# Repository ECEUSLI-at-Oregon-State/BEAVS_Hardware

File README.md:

# BEAVS_hardware

Directory contains all KiCad files for designing the BEAVS PCB.
By using these files, one can continue modifying the existing design.

All .pretty files are footprints of the devices that are the names of the files.
Back and Front png files show 3D screenshots of the front and back of the PCB design.
Additionally, all USLI BEAVS 2020 files refer to the overall PCB design from the schematic to layout.

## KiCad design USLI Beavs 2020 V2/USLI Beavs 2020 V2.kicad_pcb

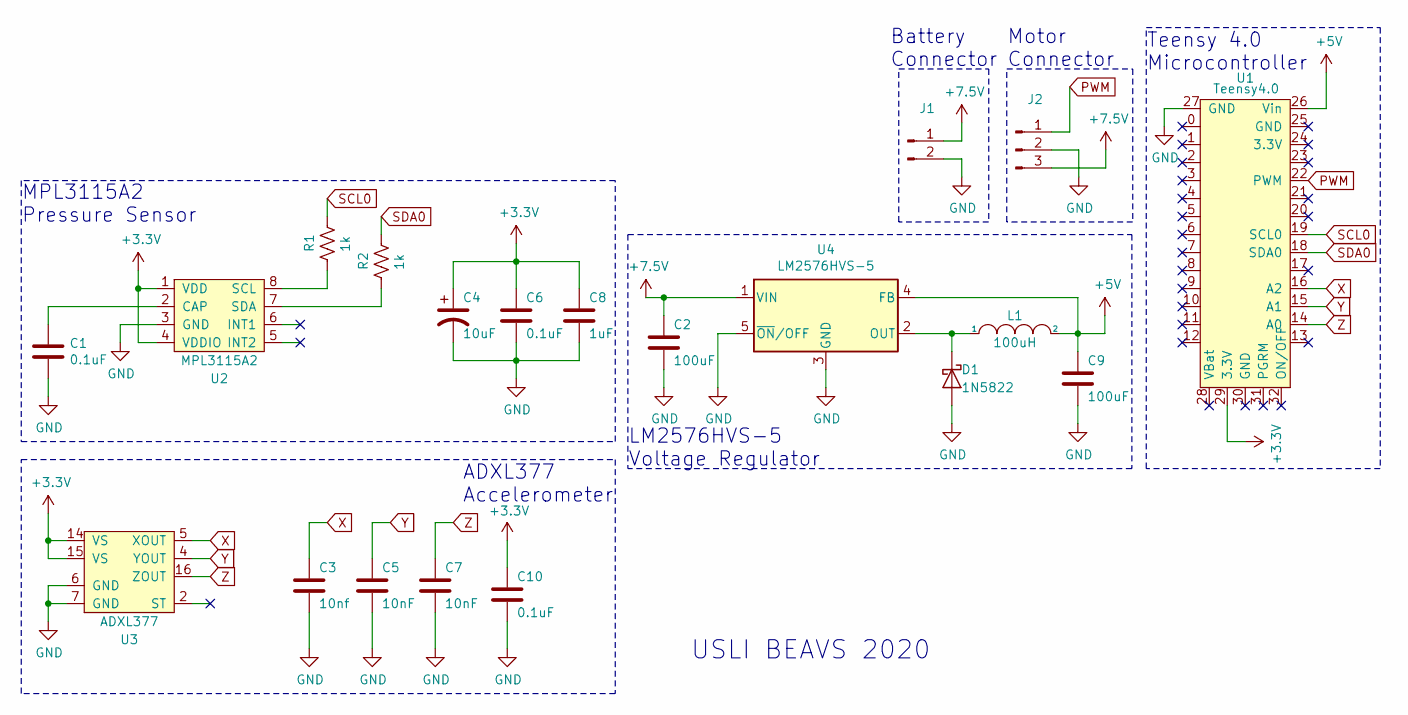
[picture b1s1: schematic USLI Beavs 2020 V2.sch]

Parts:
C1, C6, C10: 0.1uF; C_0805_2012Metric_Pad1.15x1.40mm_HandSolder
C2, C9: 100uF; elect_capacitors
C3: 10nf; C_0805_2012Metric_Pad1.15x1.40mm_HandSolder
C4: 10uF; C_0805_2012Metric_Pad1.15x1.40mm_HandSolder
C5, C7: 10nF; C_0805_2012Metric_Pad1.15x1.40mm_HandSolder
C8: 1uF; C_0805_2012Metric_Pad1.15x1.40mm_HandSolder
D1: 1N5822; IN5822
J1: vas_1x2_screw_terminal
J2: 1x3_screw_terminal
L1: 100uH; dummythiccinductor
R1, R2: 1k; R_0805_2012Metric_Pad1.15x1.40mm_HandSolder
U1: Teensy4.0; Teensy40
U2: MPL3115A2
U3: ADXL377
U4: LM2576HVS-5; TO-263-5_TabPin3

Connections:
+3V3: C4.1, C6.1, C8.1, C10.1, U1.29 (3.3V), U2.1 (VDD), U2.4 (VDDIO), U3.14 (VS), U3.15 (VS)
+5V: C9.1, L1.2, U1.26 (Vin), U4.4 (FB)
+7.5V: C2.1, J1.1, J2.3, U4.1 (VIN)
GND: C1.2, C2.2, C3.2, C4.2, C5.2, C6.2, C7.2, C8.2, C9.2, C10.2, D1.2 (A), J1.2, J2.2, U1.27 (GND), U2.3 (GND), U3.6 (GND), U3.7 (GND), U4.3 (GND), U4.5 (~ON~/OFF)
unnamed: C1.1, U2.2 (CAP)
unnamed: D1.1 (K), L1.1, U4.2 (OUT)
unnamed: R1.2, U2.8 (SCL)
unnamed: R2.2, U2.7 (SDA)
PWM: J2.1, U1.22 (PWM)
SCL0: R1.1, U1.19 (SCL0)
SDA0: R2.1, U1.18 (SDA0)
X: C3.1, U1.16 (A2), U3.5 (XOUT)
Y: C5.1, U1.15 (A1), U3.4 (YOUT)
Z: C7.1, U1.14 (A0), U3.16 (ZOUT)

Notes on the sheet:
USLI BEAVS 2020
LM2576HVS-5 Voltage Regulator
MPL3115A2 Pressure Sensor
ADXL377 Accelerometer
Teensy 4.0 Microcontroller
Battery Connector
Motor Connector

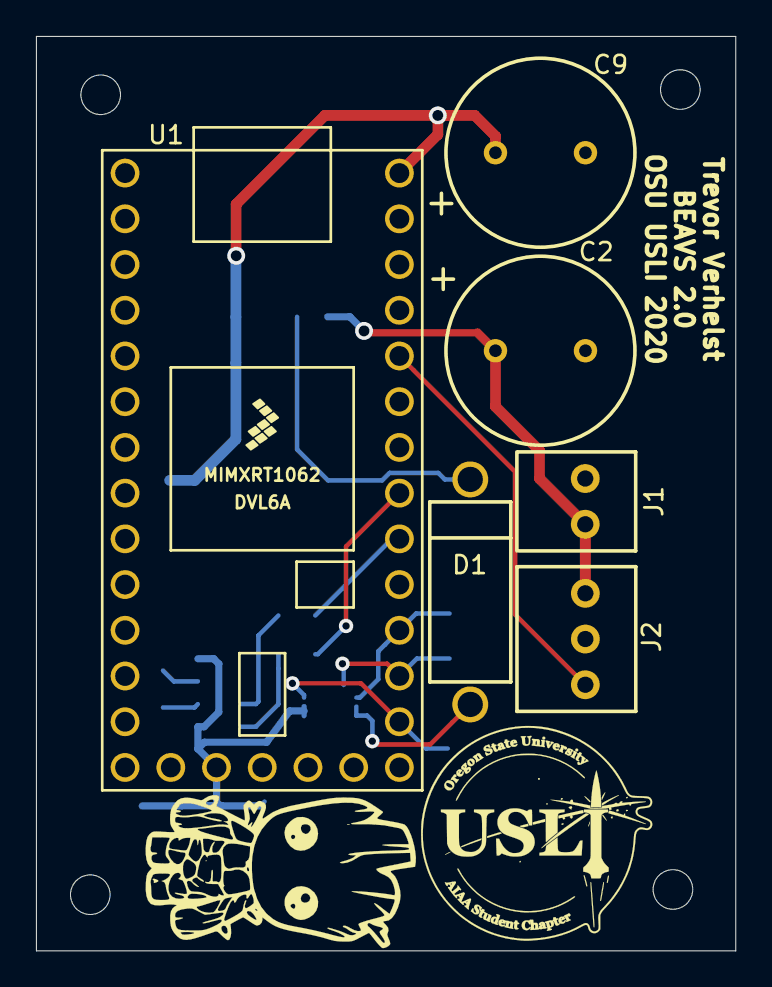
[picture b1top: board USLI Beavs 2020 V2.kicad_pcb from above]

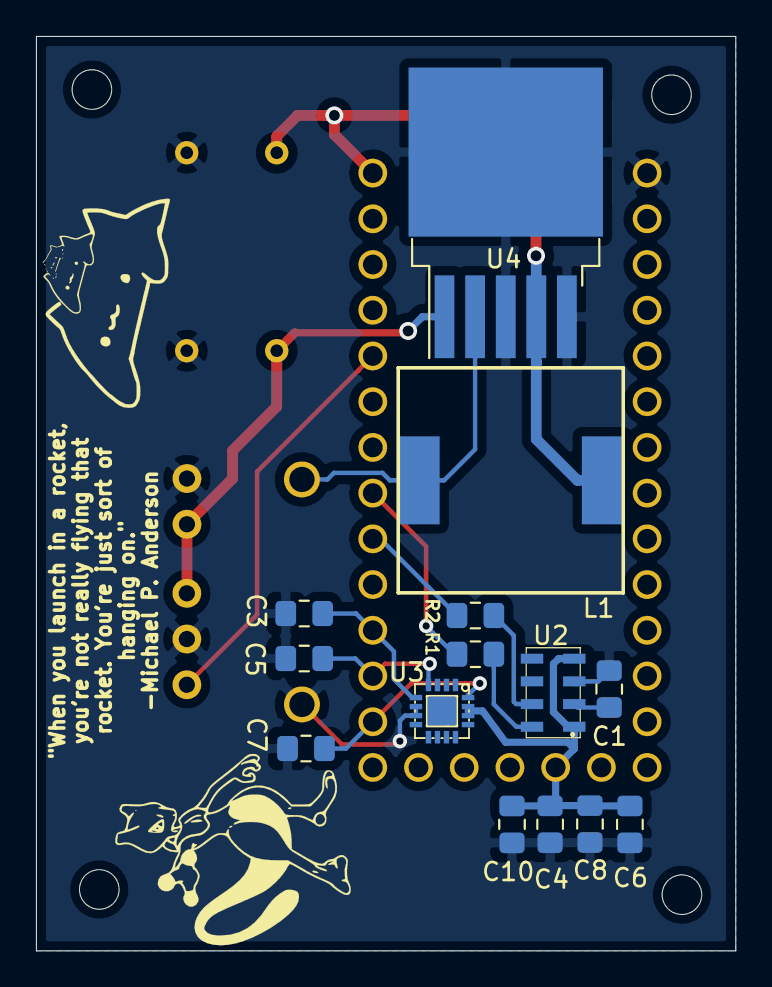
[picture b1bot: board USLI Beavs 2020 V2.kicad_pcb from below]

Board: 2 copper layers, 38.8 x 50.8 mm, 24 parts (14 on the bottom side), 14 nets.

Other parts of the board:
 : MountingHole_2.2mm_M2
 #2,  #3,  #4: MountingHole_2.2mm_M2
